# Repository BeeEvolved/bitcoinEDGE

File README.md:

# bitcoinEDGE
Open-Source Bitcoin hardware at the EDGE
### This AXE is highly experimental, and I would NOT recommend ordering parts or PCB until the design can be proven. Experimentation is the spark that ignites innovation, the cornerstone of progress, and the gateway to discovery

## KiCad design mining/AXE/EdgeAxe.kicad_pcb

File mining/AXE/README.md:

.jpg)
.jpg)

# This AXE is highly experimental, and I would NOT recommend ordering parts or PCB until the design can be proven. Experimentation is the spark that ignites innovation, the cornerstone of progress, and the gateway to discovery

This design uses the legendary open-source miner, the [Bitaxe 204](https://github.com/skot/bitaxe/tree/ultra-204), as its foundation.

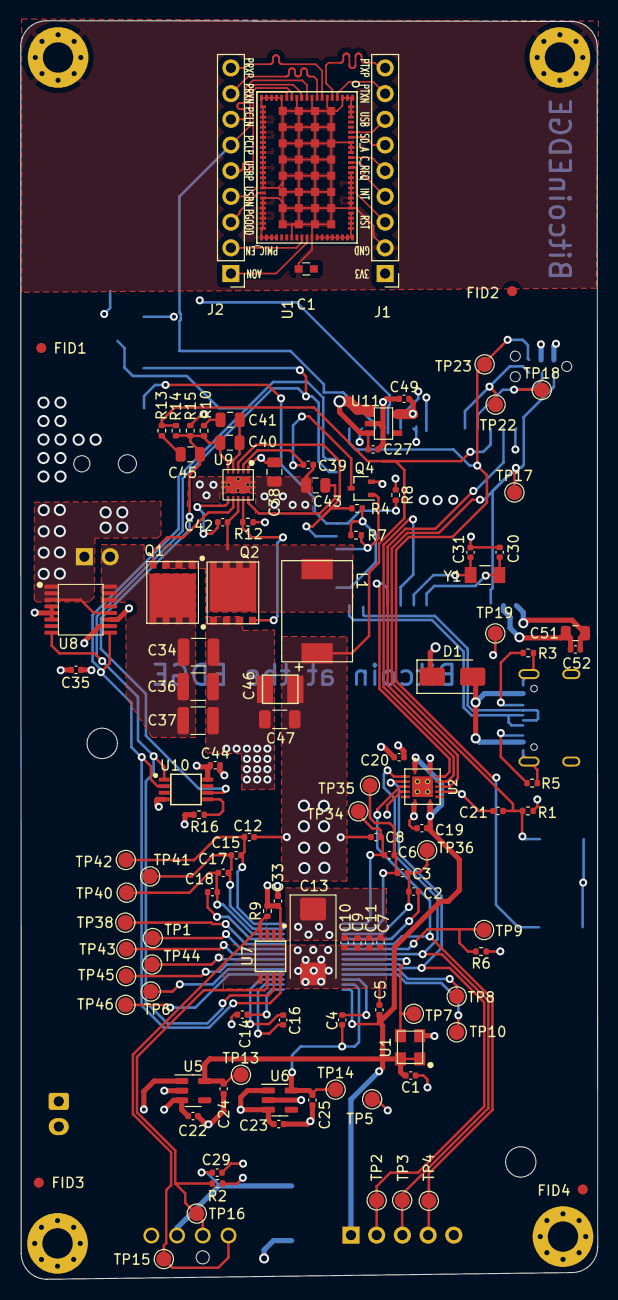
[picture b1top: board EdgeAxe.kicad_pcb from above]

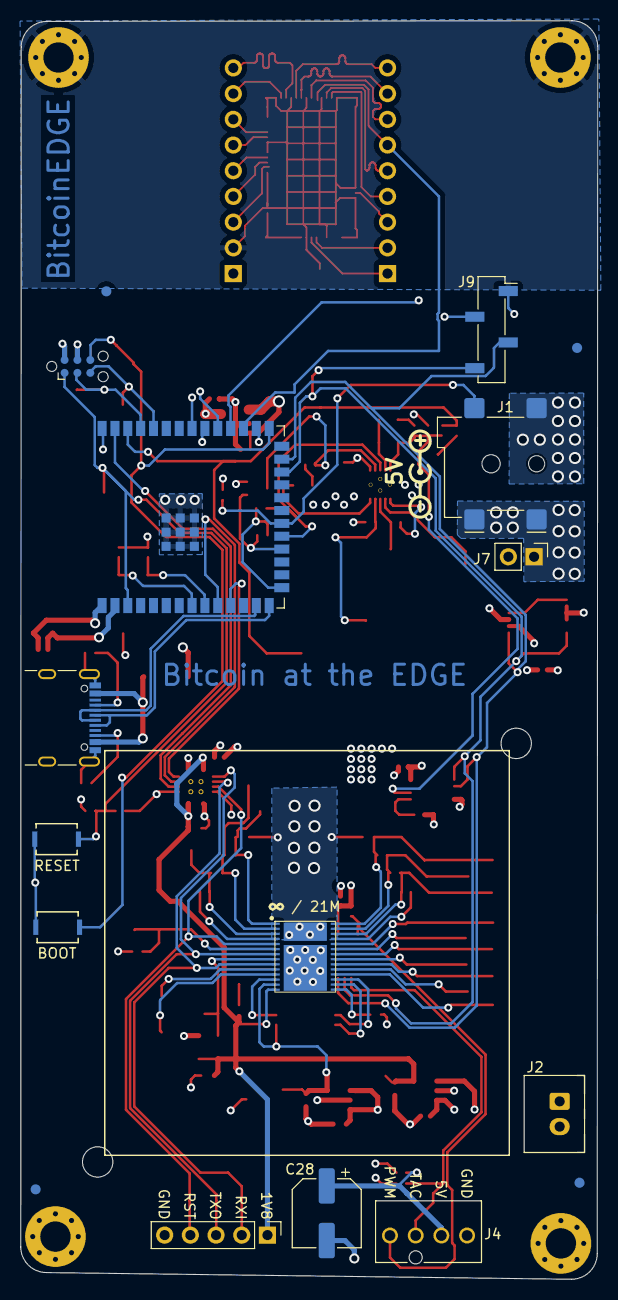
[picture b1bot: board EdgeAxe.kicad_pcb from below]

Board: 6 copper layers, 57.0 x 124.4 mm, 139 parts (18 on the bottom side), 78 nets.

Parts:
C1, C7, C9, C19, C20, C29, C33, C42, C52: 0.1uF; C_0402_1005Metric
C1#2: 100nF; C_0603
C2, C3, C4, C5, C6, C8, C10, C11, C12, C14, C15, C16, C17, C18, C21, C22, C23, C24, C25, C27, C35, C44, C49: 1uF; C_0402_1005Metric
C13: 330uF; CP_EIA-7343-31_Kemet-D_Pad2.25x2.55mm_HandSolder
C28: 220uF; CP_Elec_6.3x7.7
C30, C31: 6.8pF; C_0402_1005Metric
C34, C36, C37: 47uF; C_1210_3225Metric
C38: 1uF; C_0805_2012Metric
C39: 3.3nF; C_0402_1005Metric
C40: 180pF; C_0805_2012Metric
C41: 1.5nF; C_0805_2012Metric
C43, C51: 10uF; C_0805_2012Metric
C45: 470pF; C_0805_2012Metric
C46: 220uF; CAP_2R5TPE220MAFB
C47: 100uF; C_1206_3216Metric
D1: SS310; D_SMA
FID1, FID2, FID3, FID4, FID5, FID6, FID7, FID8: Fiducial; Fiducial_1mm_Mask2mm
H5, H6: MountingHole; MountingHole_3.5mm
H7, H8, H9, H10: MountingHole_Pad; MountingHole_3mm_Pad_Via
J1, J2: Conn_01x09_Male; Pin_Header_Straight_1x09_Pitch2.54mm
J1#2: 54-00164; BarrelJack_Wuerth_694106106102_2.0x5.5mm
J2#2: Conn_01x02; JST_XH_B2B-XH-A_1x02_P2.50mm_Vertical
J3: Conn_01x05; PinHeader_1x05_P2.54mm_Vertical
J4: Conn_01x04; 470531000
J5: TC2030-IDC; Tag-Connect_TC2030-IDC-NL_2x03_P1.27mm_Vertical
J7: Conn_01x02; PinHeader_1x02_P2.54mm_Vertical
J8: USB_C_Receptacle_USB2.0; USB_C_Receptacle_GCT_USB4105-xx-A_16P_TopMnt_Horizontal
J9: Conn_01x04; PinSocket_1x04_P2.54mm_Vertical_SMD_Pin1Right
L1: 150nH; FP1005R1-R15-R
Q1, Q2: CSD17311Q5
Q4: 2N7002K; SOT-323_SC-70
R1, R4, R6, R7, R9: 10k; R_0402_1005Metric
R2: 5.6k; R_0402_1005Metric
R3, R5: 5.1k; R_0402_1005Metric
R8: 1M; R_0402_1005Metric
R10: 3.83k; R_0402_1005Metric
R12: 4.12k; R_0402_1005Metric
R13: 1.33k; R_0402_1005Metric
R14: 4.99k; R_0402_1005Metric
R15: 3.32k; R_0402_1005Metric
R16: 80.6k; R_0402_1005Metric
SW1, SW2: GT-TC029B-H025-L1N; SW_CS1213AGF260_CRS
TP1, TP2, TP3, TP4, TP5, TP6, TP7, TP8, TP9, TP10, TP13, TP14, TP15, TP16, TP17, TP18, TP19, TP22, TP23, TP34, TP35, TP36, TP38, TP40, TP41, TP42, TP43, TP44, TP45, TP46: TestPoint; TestPoint_Pad_D1.5mm
U1: 25MHz; O 25,0-JO32-B-1V3-1-T1-LF
U1#2: Coral_1; LGA120
U2: TXB0104RGYR; TXB0104
U3: polarity
U5: MCP1824T-1802E; SOT-23-5
U6: MCP1824T-0802E; SOT-23-5
U7: EMC2101; TSSOP-8_3x3mm_P0.65mm
U8: INA260; TSSOP-16_4.4x5mm_P0.65mm
U9: TPS40305
U10: DS4432U+; TSSOP-8_3x3mm_P0.65mm
U11: RT9080-33GJ5
U12: ESP32-S3-WROOM-1
U14: BM1366_mode1; BM1366
Y1: 32.768kHz; SC32S-7PF20PPM

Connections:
+3V3: U1#2.56, U1#2.57, U1#2.58, U1#2.59, U1#2.60, U1#2.61, U1#2.62, U1#2.63, U1#2.64, U1#2.65, U1#2.66, U1#2.67
/3V3: C20.1, C33.1, C35.1, C44.1, C49.1, C51.1, C52.1, J1.1, J5.2, J9.2, R1.1, R2.2, R4.1, R7.1, R8.1, R9.2, TP19.1, U2.14 (VCCB), U7.1 (VDD), U8.10 (VS), U10.8 (VCC), U11.5 (VOUT), U12.2 (3V3), U12.15 (GPIO3/TOUCH3/ADC1_CH2*)
/5V: C22.1, C23.1, C27.1, C28.1, C29.1, C34.1, C36.1, C37.1, C38.1, D1.1, J2#2.2, J4.2, J7.2, Q1.5 (D), U5.1 (VIN), U5.3 (EN), U6.1 (VIN), U6.3 (EN), U8.14 (IN-), U8.15 (IN-), U8.16 (IN-), U9.1 (VDD), U11.1 (VIN), U11.3 (EN)
/BM1366/0V8: C4.1, C25.1, TP14.1, U6.5 (VOUT), U14.13 (VDDIO_08_0)
/BM1366/1V8: C1.2, C5.1, C19.1, C24.1, J3.1, TP13.1, U1.1 (EN), U1.4 (VIN), U2.1 (VCCA), U2.8 (OE), U5.5 (VOUT), U14.14 (VDDIO_18_0)
/BM1366/ADDR0: TP8.1, U14.10 (ADDR0)
/BM1366/ADDR1: TP10.1, U14.11 (ADDR1)
/BM1366/BI: R6.2, TP9.1, U14.6 (BI)
/BM1366/BO: TP1.1, U14.23 (BO)
/BM1366/CI: J3.2, TP2.1, U2.3 (A2), U14.9 (CI)
/BM1366/CLKI: TP7.1, U1.3 (OUT), U14.8 (CLKI)
/BM1366/CLKO: TP44.1, U14.21 (CLKO)
/BM1366/CO: TP45.1, U14.20 (CO)
/BM1366/INV_CLKO: TP6.1, U14.19 (INV_CLKO)
/BM1366/NRSTO: TP38.1, U14.24 (NRSTO)
/BM1366/PIN_MODE: TP46.1, U14.18 (PIN_MODE)
/BM1366/RI: TP43.1, U14.22 (RI)
/BM1366/RO: J3.3, TP3.1, U2.2 (A1), U14.7 (RO)
/BM1366/RST_N: J3.4, TP4.1, U2.4 (A3), U14.5 (NRSTI)
/BM1366/VDD1_0: C6.2, C8.1, TP34.1, U14.1 (VDD1_0)
/BM1366/VDD1_1: C12.2, C15.1, TP42.1, U14.28 (VDD1_1)
/BM1366/VDD2_0: C3.2, C6.1, TP35.1, U14.2 (VDD2_0)
/BM1366/VDD2_1: C15.2, C17.1, TP41.1, U14.27 (VDD2_1)
/BM1366/VDD3_0: C2.2, C3.1, TP36.1, U14.3 (VDD3_0)
/BM1366/VDD3_1: C17.2, C18.1, TP40.1, U14.26 (VDD3_1)
/ESP32/EN: C21.1, J5.1, R1.2, SW1.2, TP17.1, U12.3 (EN)
/ESP32/IO0: J5.6, SW2.2, TP23.1, U12.27 (GPIO0/BOOT*)
/ESP32/PWR_EN: Q4.1 (G), R7.2, U12.18 (GPIO10/TOUCH10/ADC1_CH9/FSPICS0/FSPIIO4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)
/ESP32/P_RX: J5.5, TP22.1, U12.36 (U0RXD/GPIO44/CLK_OUT2)
/ESP32/P_TX: J5.3, TP18.1, U12.37 (U0TXD/GPIO43/CLK_OUT1)
/ESP32/XIN32: C30.1, U12.8 (GPIO15/U0RTS/ADC2_CH4/XTAL_32K_P), Y1.1
/ESP32/XOUT32: C31.1, U12.9 (GPIO16/U0CTS/ADC2_CH5/XTAL_32K_NH5), Y1.2
/Fan/FAN_PWM: J4.4, R9.1, TP15.1, U7.4 (FAN)
/Fan/FAN_TACH: J4.3, R2.1, TP16.1, U7.6 (ALERT/TACH)
/PLUG_SENSE: J1#2.3, R8.2, U12.20 (GPIO12/TOUCH12/ADC2_CH1/FSPICLK/FSPIIO6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)
/Power/OUT0: C40.2, C45.2, R10.2, R14.2, R15.1, U9.5 (FB), U10.6 (OUT0)
/Power/PGOOD: R4.2, U9.3 (PGOOD), U12.19 (GPIO11/TOUCH11/ADC2_CH0/FSPID/FSPIIO5/S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)
/Power/SW: C42.2, L1.1, Q1.1, Q1.2, Q1.3 (S), Q2.5 (D), U9.8 (SW)
/Power/VIN: J1#2.1, J7.1, U8.1 (IN+), U8.2 (IN+), U8.3 (IN+), U8.12 (VBUS)
/RST: U2.11 (B3), U12.39 (GPIO1/TOUCH1/ADC1_CH0)
/RX: U2.13 (B1), U12.11 (GPIO18/U1RXD/ADC2_CH7/CLK_OUT3)
/SCL: J9.3, U7.8 (SMCLK), U8.9 (SCL), U10.2 (SCL), U12.25 (GPIO48/SPICLK_N/SUBSPICLK_N_DIFF)
/SDA: J9.4, U7.7 (SMDATA), U8.8 (SDA), U10.1 (SDA), U12.24 (GPIO47/SPICLK_P/SUBSPICLK_P_DIFF)
/TX: U2.12 (B2), U12.10 (GPIO17/U1TXD/ADC2_CH6)
/VDD: C7.1, C8.2, C9.1, C10.1, C11.1, C12.1, C13.1, C46.1, C47.1, L1.2, R13.1, R14.1, U12.38 (GPIO2/TOUCH2/ADC1_CH1), U14.29 (VDD)
AON: J2.1, U1#2.54
CLKREQ_L: J1.5, U1#2.78, U12.33 (MTDO/GPIO40/CLK_OUT2)
GND: C1.1, C1#2.2, C2.1, C4.2, C5.2, C7.2, C9.2, C10.2, C11.2, C13.2, C14.2, C16.2, C18.2, C19.2, C20.2, C21.2, C22.2, C23.2, C24.2, C25.2, C27.2, C28.2, C29.2, C30.2, C31.2, C33.2, C34.2, C35.2, C36.2, C37.2, C38.2, C39.2, C43.2, C44.2, C46.2, C47.2, C49.2, C51.2, C52.2, H7.1, H8.1, H9.1, H10.1, J1.2, J1#2.2, J2#2.1, J3.5, J4.1, J5.4, J8.A1 (GND), J8.A12 (GND), J8.B1 (GND), J8.B12 (GND), J8.S1 (SHIELD), J9.1, Q2.1, Q2.2, Q2.3 (S), Q4.2 (S), R3.1, R5.1, R6.1, R12.2, R15.2, R16.2, SW1.1, SW2.1, TP5.1, U1.2 (GND), U1#2.1, U1#2.2, U1#2.3, U1#2.6, U1#2.9, U1#2.12, U1#2.15, U1#2.16, U1#2.17, U1#2.18, U1#2.19, U1#2.20, U1#2.21, U1#2.22, U1#2.23, U1#2.24, U1#2.25, U1#2.26, U1#2.27, U1#2.28, U1#2.29, U1#2.30, U1#2.31, U1#2.32, U1#2.33, U1#2.34, U1#2.35, U1#2.36, U1#2.38, U1#2.39, U1#2.40, U1#2.41, U1#2.42, U1#2.43, U1#2.44, U1#2.45, U1#2.46, U1#2.47, U1#2.48, U1#2.51, U1#2.55, U1#2.68, U1#2.69, U1#2.70, U1#2.71, U1#2.72, U1#2.73, U1#2.74, U1#2.75, U1#2.79, U1#2.80, U1#2.81, U1#2.86, U1#2.87, U1#2.88, U1#2.89, U1#2.90, U1#2.91, U1#2.92, U1#2.93, U1#2.94, U1#2.95, U1#2.96, U1#2.97, U1#2.98, U1#2.99, U1#2.100, U1#2.101, U1#2.102, U1#2.103, U1#2.104, U1#2.105, U1#2.106, U1#2.107, U1#2.108, U1#2.109, U1#2.110, U1#2.111, U1#2.112, U1#2.113, U1#2.114, U1#2.115, U1#2.116, U1#2.117, U1#2.118, U1#2.119, U1#2.120, U2.5 (A4), U2.7 (GND), U2.10 (B4), U2.15 (GND), U2.16 (GND), U2.17 (GND), U2.18 (GND), U2.19 (GND), U5.2 (GND), U6.2 (GND), U7.5 (GND), U8.4 (A1), U8.5 (A0), U8.6 (GND), U8.11 (GND), U9.11 (GND), U10.4 (GND), U11.2 (GND), U12.1 (GND), U12.40 (GND), U12.41 (GND), U14.4 (VSS), U14.12 (PLL_VSS), U14.17 (VSS), U14.25 (VSS), U14.30 (VSS)
INTR: J1.4, U1#2.77
unnamed: C41.2, R10.1
unnamed: C45.1, R13.2
unnamed: D1.2, J8.A4 (VBUS), J8.A9 (VBUS), J8.B4 (VBUS), J8.B9 (VBUS)
unnamed: J8.A5 (CC1), R3.2
unnamed: J8.B5 (CC2), R5.2
unnamed: Q1.4 (G), U9.7 (HDRV)
unnamed: Q2.4 (G), R12.1, U9.9 (LDRV)
unnamed: C39.1, Q4.3 (D), U9.2 (EN/SS)
unnamed: C42.1, U9.6 (BOOT)
unnamed: C43.1, U9.10 (BP)
unnamed: C40.1, C41.1, U9.4 (COMP)
unnamed: R16.1, U10.5 (FS0)
unnamed: J8.A7 (D-), J8.B7 (D-), U12.13 (GPIO19/U1RTS/ADC2_CH8/CLK_OUT2/USB_D-)
unnamed: J8.A6 (D+), J8.B6 (D+), U12.14 (GPIO20/U1CTS/ADC2_CH9/CLK_OUT1/USB_D+)
unnamed: C16.1, U14.16 (VDDIO_08_1)
unnamed: C14.1, U14.15 (VDDIO_18_1)
PCIE_REFCLK_N: J2.7, U1#2.10
PCIE_REFCLK_P: J2.6, U1#2.11, U12.29 (SPIIO7/GPIO36/FSPICLK/SUBSPICLK)
PCIE_RX_N: J2.8, U1#2.8, U12.30 (SPIDQS/GPIO37/FSPIQ/SUBSPIQ)
PCIE_RX_P: J2.9, U1#2.7
PCIE_TX_N: J1.8, U1#2.4, U12.28 (SPIIO6/GPIO35/FSPID/SUBSPID)
PCIE_TX_P: J1.9, U1#2.5
PGOOD4: J2.3, U1#2.37
PMIC_EN: J2.2, U1#2.53, U12.32 (MTCK/GPIO39/CLK_OUT3/SUBSPICS1)
RST_L: J1.3, U1#2.76, U12.31 (GPIO38/FSPIWP/SUBSPIWP)
SD_ALARM: J1.6, U1#2.82
USB2_D_N: J2.4, U1#2.14
USB2_D_P: J2.5, U1#2.13
USB_SEL: J1.7, U1#2.83

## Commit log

2024-05-12 Create LICENSE
2024-05-17 cleanup
